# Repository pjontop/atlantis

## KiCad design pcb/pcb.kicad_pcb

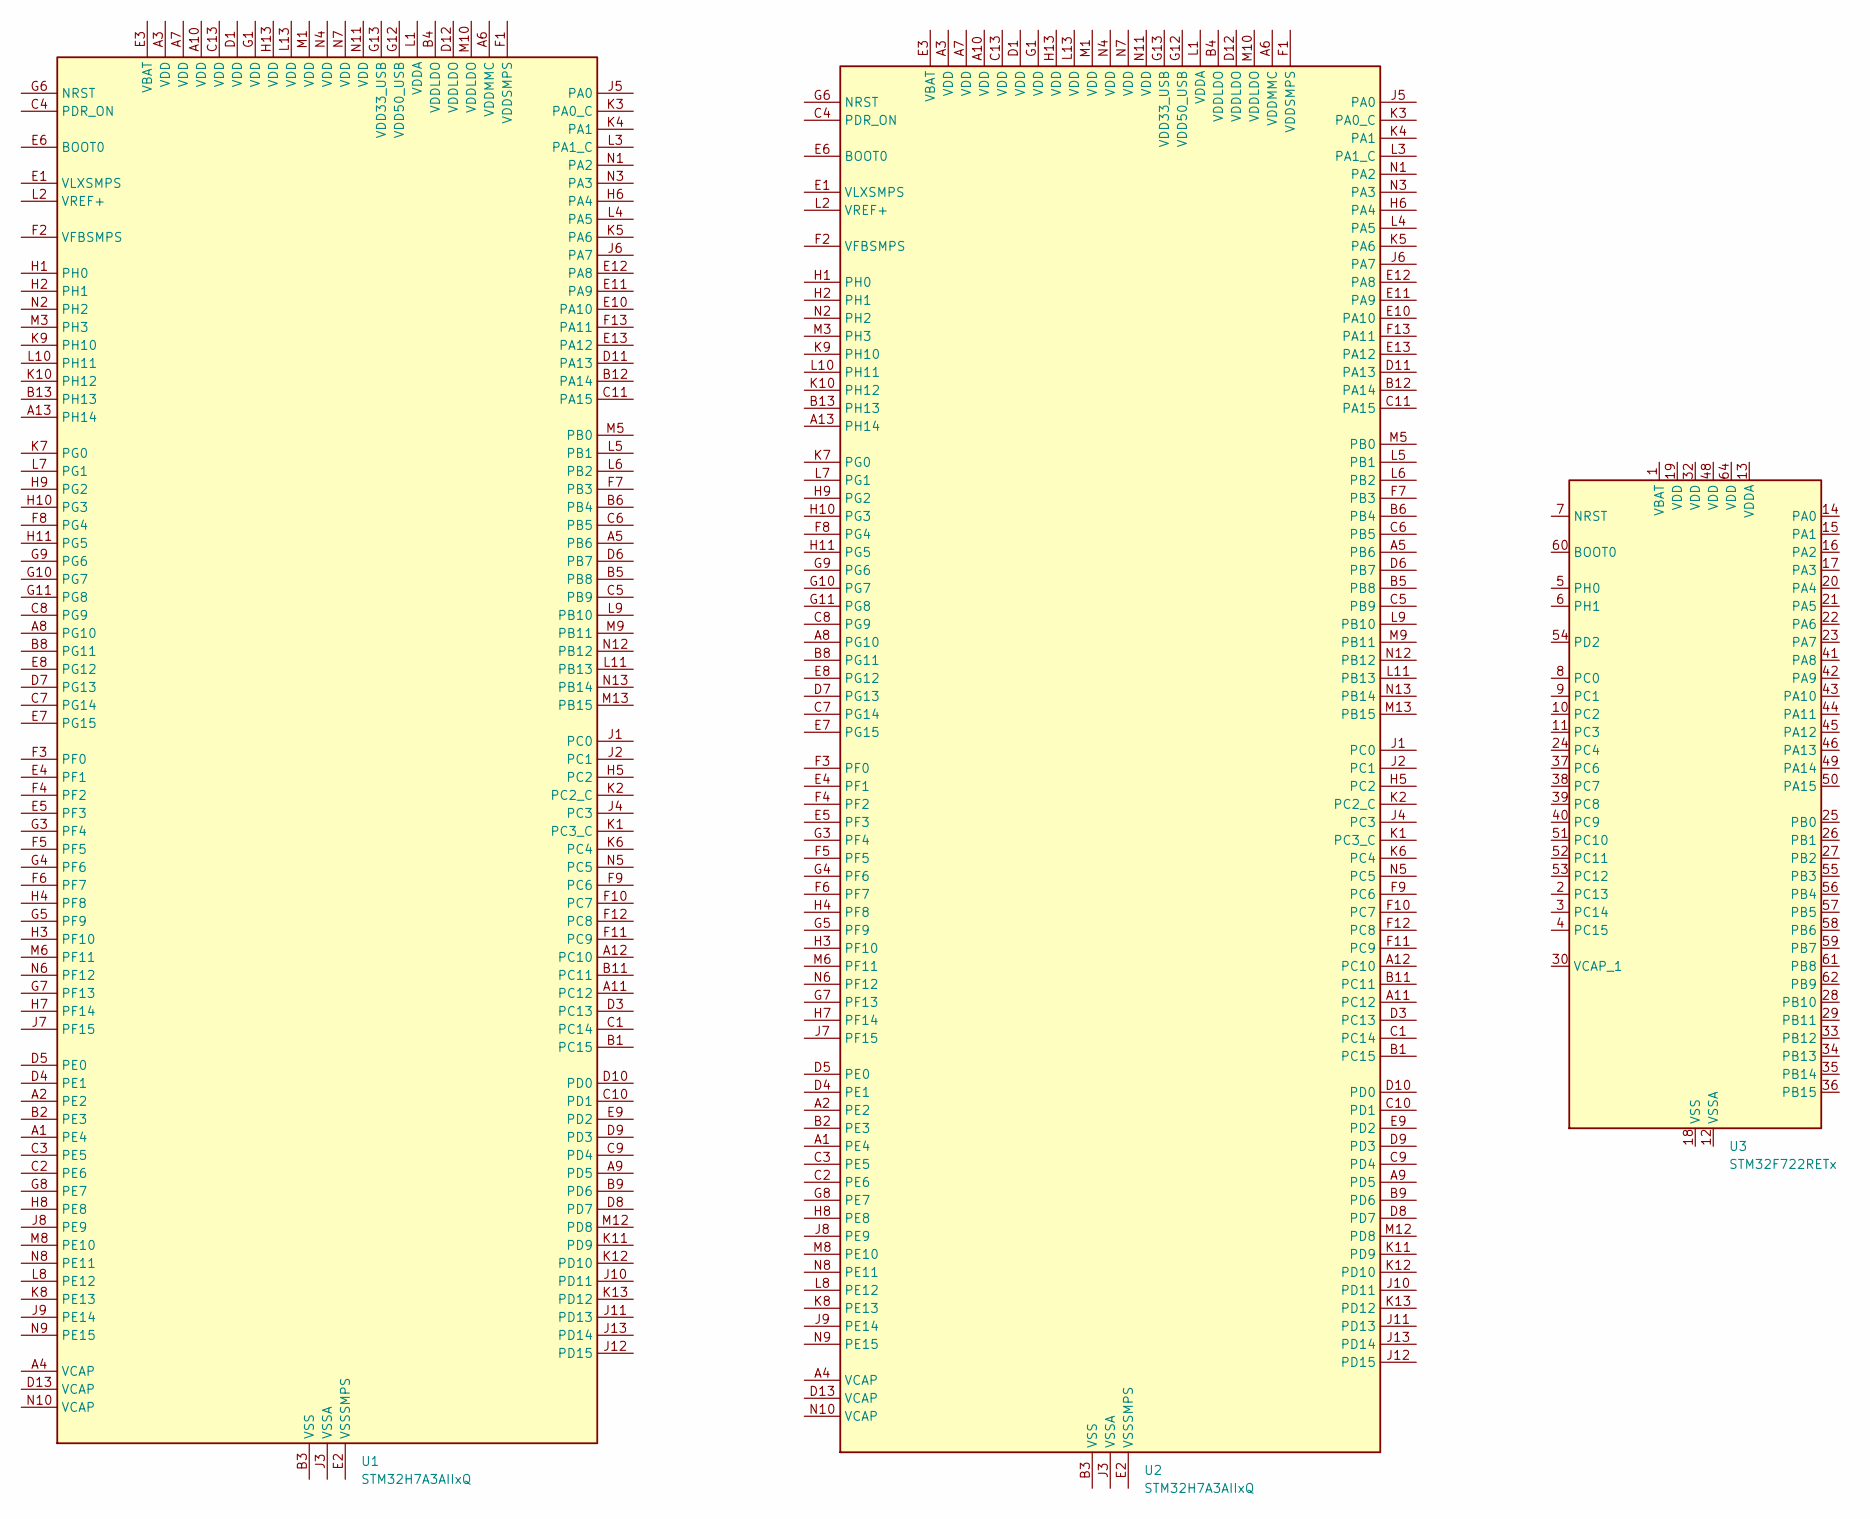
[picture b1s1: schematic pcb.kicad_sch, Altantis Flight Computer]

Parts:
U1, U2: STM32H7A3AIIxQ; UFBGA-169_7x7mm_Layout13x13_P0.5mm
U3: STM32F722RETx; LQFP-64_10x10mm_P0.5mm

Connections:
unnamed: U1.B3 (VSS), U1.B7 (VSS), U1.B10 (VSS), U1.C12 (VSS), U1.D2 (VSS), U1.G2 (VSS), U1.H12 (VSS), U1.L12 (VSS), U1.M2 (VSS), U1.M4 (VSS), U1.M7 (VSS), U1.M11 (VSS)
unnamed: U2.B3 (VSS), U2.B7 (VSS), U2.B10 (VSS), U2.C12 (VSS), U2.D2 (VSS), U2.G2 (VSS), U2.H12 (VSS), U2.L12 (VSS), U2.M2 (VSS), U2.M4 (VSS), U2.M7 (VSS), U2.M11 (VSS)
unnamed: U3.18 (VSS), U3.31 (VSS), U3.47 (VSS), U3.63 (VSS)

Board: 2 copper layers, 3 parts (0 on the bottom side), 3 nets, no tracks yet.
